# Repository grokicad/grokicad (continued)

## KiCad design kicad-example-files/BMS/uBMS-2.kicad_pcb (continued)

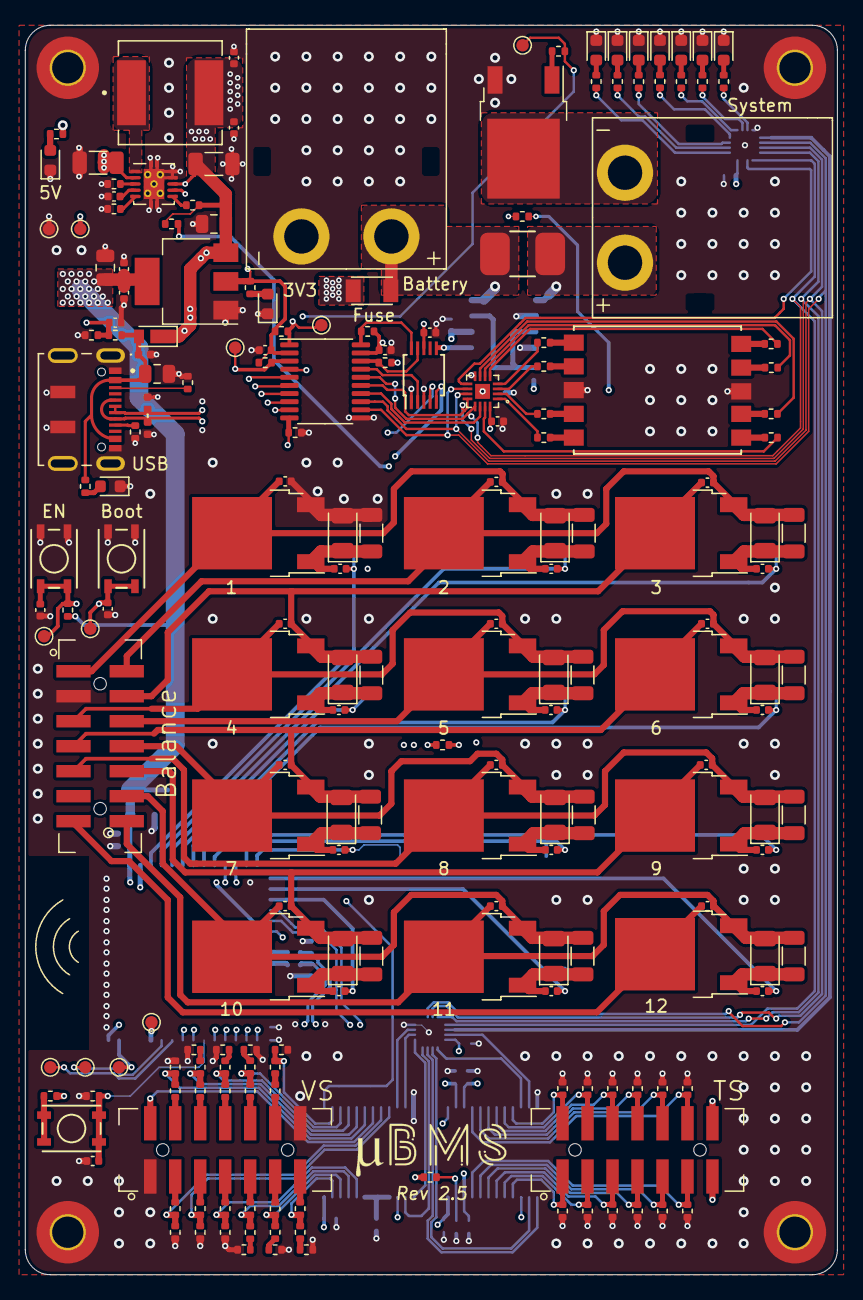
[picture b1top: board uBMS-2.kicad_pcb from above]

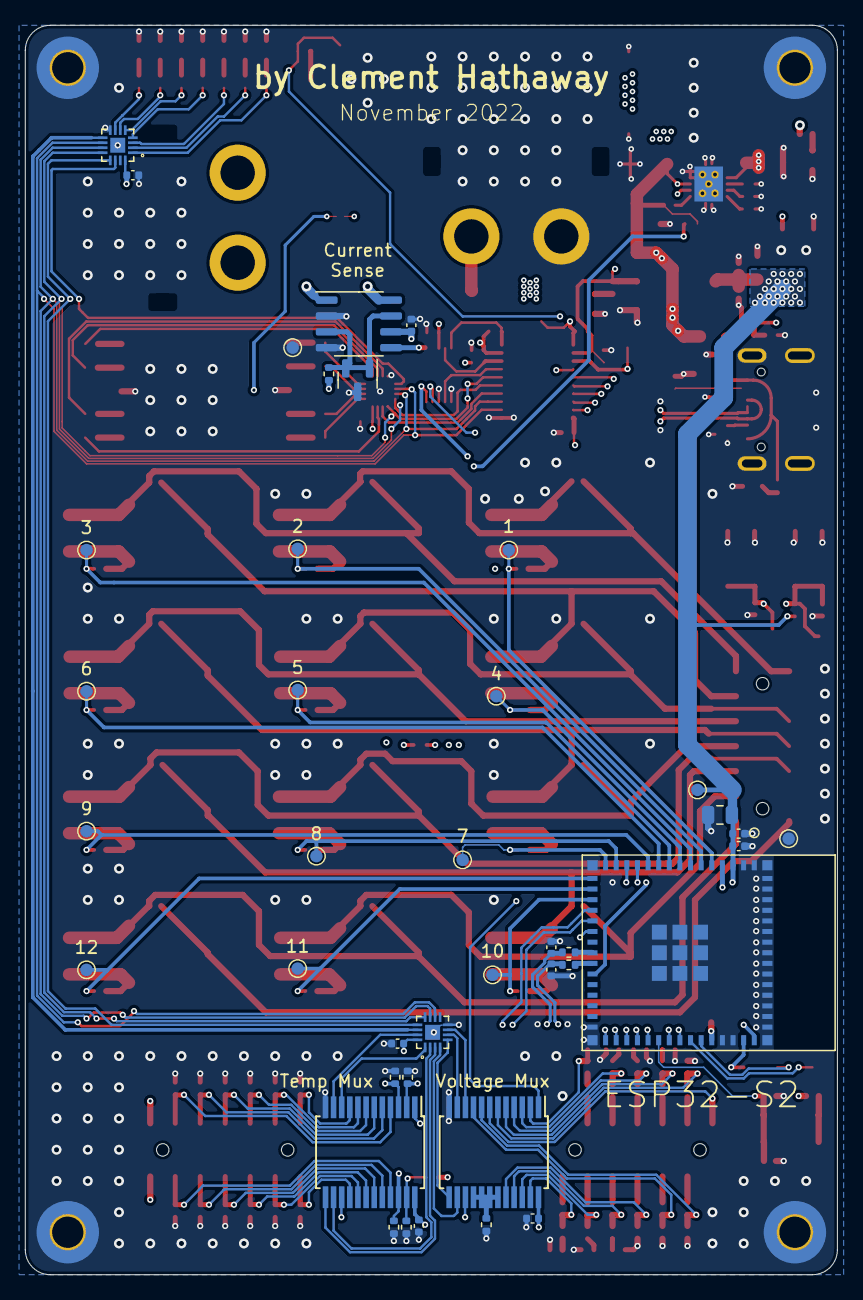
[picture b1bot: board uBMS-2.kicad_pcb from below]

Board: 4 copper layers, 65.0 x 100.0 mm, 245 parts (40 on the bottom side), 179 nets.

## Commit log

2025-12-07 database interface
2025-12-07 yellow scrollbar
2025-12-07 add git panel mockl
2025-12-07 Added messages that'll serialize to curl call
2025-12-07 compiles on ec2
2025-12-07 update lockfile
2025-12-07 running remotely
2025-12-07 added bms example
2025-12-07 refactored database and added swagger
2025-12-07 frontend and backend happy again
2025-12-07 testing
2025-12-07 trying to visualize non-kicad commits
2025-12-07 up lockfile
2025-12-07 correctly collapses non-kicad commits
2025-12-07 add json payload to the grok button
2025-12-07 fix linter errors and warnings
2025-12-07 clean error page
2025-12-07 Add response API to xAI client
2025-12-07 Try adding Responses API to grok for endpoint to commit
2025-12-07 upgrade wrangler
2025-12-07 Fix silly missing include
2025-12-07 full api for python distillation
2025-12-07 fix race condition
2025-12-07 Fixed mirror bug on certain symbol which made incorrect json connections
2025-12-07 sidebar
2025-12-07 Update Grok API request type and enhance HTML files with meta tags and favicon
2025-12-07 massively improve chat ui
2025-12-07 cache clear is back
2025-12-07 fix backend reliablility and improve system prompt
2025-12-07 fix favicon
2025-12-07 add venv
2025-12-07 examples
2025-12-07 Add readme
2025-12-07 added website link to readme
2025-12-07 Added images
2025-12-07 Update README.md
    reorder images
